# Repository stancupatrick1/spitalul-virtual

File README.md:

<p align="center">
  🌐 <b><a href="https://stancupatrick1.github.io/spitalul-virtual/">stancupatrick1.github.io/spitalul-virtual</a></b> – website, sign-up and live dashboard
</p>

<p align="center">
  <b>Spitalul Virtual</b> (“The Virtual Hospital”) is an open-source health wearable platform.<br>
  It comes in two versions – a <b>smartwatch</b> with a round screen and a slim, <b>screenless band</b> – both built from scratch:<br>
  custom black PCB, silicone case with straps, firmware and a phone web app.
</p>

---

## ✨ Two devices, one platform

<table>
  <tr>
    <th width="50%">⌚ Spitalul Virtual Watch</th>
    <th width="50%">📿 Spitalul Virtual Band</th>
  </tr>
  <tr>
    <td></td>
    <td></td>
  </tr>
  <tr>
    <td>
      <ul>
        <li>1.28" round colour display (GC9A01)</li>
        <li>Heart rate + blood oxygen (MAX30102)</li>
        <li>Step counter (LIS3DH)</li>
        <li>Ø 42 mm round black PCB</li>
        <li>Pod Ø 46.8 × 14 mm, ~250 mAh</li>
      </ul>
    </td>
    <td>
      <ul>
        <li>No screen – LED, vibration and phone app</li>
        <li>Heart rate + SpO2 + <b>skin temperature (TMP117, ±0.1 °C)</b></li>
        <li>Step counter (LIS3DH)</li>
        <li>40 × 24 mm black PCB</li>
        <li>Pod 44 × 28 × 11 mm, ~110 mAh</li>
      </ul>
    </td>
  </tr>
  <tr>
    <td align="center"><a href="watch/"><b>→ watch/</b></a></td>
    <td align="center"><a href="band/"><b>→ band/</b></a></td>
  </tr>
</table>

Both run on an **ESP32-C3** (WiFi + Bluetooth LE), charge over **USB-C** and stream their data to your phone over Bluetooth using the standard Heart Rate, Pulse Oximeter and Health Thermometer services.

## 📱 All-day data in Health Connect (Android) – 🚧 in development

> **🚧 În dezvoltare / In development** – not ready for users yet (not tested on a real band, ROOK upload not connected yet).

The band saves **one record per minute, all day** (the last ~40–45 days). The **[Spitalul Virtual Android app](companion/)** downloads it over Bluetooth and writes it to **Health Connect**. From there the Spitalul Virtual platform imports it through ROOK, like data from any other watch.

```
band ──Bluetooth──▶ Spitalul Virtual app ──▶ Health Connect ──ROOK──▶ Spitalul Virtual platform
```

Test build: **[app-latest](https://github.com/stancupatrick1/spitalul-virtual/releases/tag/app-latest)** (built automatically by GitHub Actions) · step-by-step instructions (RO): [`companion/README.md`](companion/README.md) · protocol: [`band/docs/SYNC_PROTOCOL.md`](band/docs/SYNC_PROTOCOL.md)

## 🔬 The boards

| Watch – skin side | Band – skin side |
|:---:|:---:|
|  |  |

* 2 layers, 1.0 mm, **black solder mask**, white silkscreen, ENIG (gold) pads
* sensors on the skin side, battery side under the cells
* KiCad design-rule check: **0 errors, 0 unconnected pads**
* ready-to-order files for JLCPCB / PCBWay: Gerbers, BOM with LCSC part numbers, pick-and-place

## 🧩 What's inside

```
spitalul-virtual/
├── watch/                    ⌚ smartwatch with a round screen
│   ├── hardware/kicad/       KiCad 7 project (schematic, PCB, footprints, 3D models)
│   ├── hardware/jlcpcb/      Gerbers, BOM, CPL – ready to order
│   ├── mechanical/           silicone case + straps (OpenSCAD, STL), mold, PCB STEP
│   ├── firmware/             ESP32-C3 firmware (PlatformIO / Arduino)
│   └── docs/                 schematic PDF, ordering guide, build guide
└── band/                     📿 slim screenless band
    ├── hardware/  mechanical/  firmware/  docs/   (same layout)
    └── app/                  web app – live data over Web Bluetooth
companion/                    📱 Android app (Flutter): band → Health Connect
```

Every design file is generated from one Python description of the circuit (`*/scripts/design.py`), so the schematic and the PCB always match – run `scripts/make_all.sh` to rebuild a board from scratch.

## 🚀 Build one

1. **Order the PCB** – follow [`watch/docs/ORDERING_JLCPCB.md`](watch/docs/ORDERING_JLCPCB.md) or [`band/docs/ORDERING_JLCPCB.md`](band/docs/ORDERING_JLCPCB.md)
2. **Print or cast the case** – `mechanical/stl/` (TPU 85A–95A or platinum silicone)
3. **Flash the firmware** – `cd firmware && pio run -t upload`
4. **Open the app** – `band/app/index.html` in Chrome, tap *Conectează brățara*

| | |
|:---:|:---:|
|  |  |

## 🗺️ Roadmap

- [x] Schematic + PCB for the watch and the band
- [x] Silicone case, straps and casting molds
- [x] Firmware (heart rate, SpO2, steps, temperature, BLE) and web app
- [ ] First prototype boards
- [ ] Testing on the wrist and calibration
- [x] All-day history on the band + Android app that saves it to Health Connect
- [ ] Test the full path on the Spitalul Virtual platform (ROOK → „Preia din dispozitive”)

## 👋 About us

### Hi, I'm Patrick

I'm **Stancu Patrick**, a middle-school student at **Colegiul Național „Mihai Viteazul” Ploiești**, Romania, who loves building electronics that help people.

| Year | Olimpiada Națională de Creativitate Științifică | Project |
|:---:|:---|:---|
| 🥇 2024 | **Winner** | **SmartBuoy** |
| 🏅 2025 | **Mențiune** (Honourable Mention) | [**ThermoGuard**](https://github.com/stancupatrick1/thermoguard) – ESP32 temperature monitoring for medical fridges and freezers |
| 🔧 2026 | building now | **Spitalul Virtual** – this project |

More of my projects: [ThermoGuard](https://github.com/stancupatrick1/thermoguard) · [PEEPER](https://github.com/stancupatrick1/Project_Peeper) · [my GitHub profile](https://github.com/stancupatrick1)

### Hi, I'm Nicola 👋

I'm a middle-school student at **Colegiul Național „Mihai Viteazul” Ploiești**, Romania. I love learning new things and getting better at them, and right now that means building electronics that help people.

* 🔧 Working on [Spitalul Virtual](https://github.com/stancupatrick1/spitalul-virtual) with my team: improving our open-source health wearables (a smartwatch and a screenless band) and building the phone app that sends their data to a doctor
* 🇷🇴 Based in Ploiești, Romania · I write in English and Romanian

[Nicola's GitHub profile](https://github.com/NicolaGrigore2012)

## ⚠️ Disclaimer

This is a student/hobby project. Heart-rate, SpO2 and temperature readings are estimates and are **not** for medical use or diagnosis.

## 📄 License

[MIT](LICENSE) © 2026 Stancu Patrick – use it, learn from it, build your own.

<p align="center"><sub>made with ❤️ in Romania by Stancu Patrick</sub></p>

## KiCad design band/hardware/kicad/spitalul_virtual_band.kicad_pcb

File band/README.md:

# Spitalul Virtual – Band

**made by Stancu Patrick**

A slim, **screenless** wearable, the little sibling of the Spitalul Virtual smartwatch. It has the same **black PCB** style and the same brains, plus a **skin temperature sensor**:

* ❤️ **heart rate** + 🩸 **blood oxygen (SpO2)** – MAX30102
* 🌡️ **skin temperature** (±0.1 °C) – TMP117
* 👣 **steps** – LIS3DH accelerometer
* 🔋 **USB-C charging**, 📳 vibration motor, 🟢 status LED, side button
* 📱 everything streams to your phone over **Bluetooth LE** (web app included)

| Board – skin side | Board – battery side |
|---|---|
|  |  |

> ⚠️ Hobby project. Heart-rate, SpO2 and temperature values are estimates and are **not** for medical use. The temperature is **skin** temperature (normally 32–35 °C), not body temperature.

---

## Size

| | Watch | **Band** |
|---|---|---|
| Board | Ø 42 mm round | **40 × 24 mm** pill |
| Pod | Ø 46.8 × 14 mm | **44.4 × 28.4 × 11 mm** |
| Screen | 1.28" round | none – LED + vibration + phone app |
| Battery | 402530 (~250 mAh) | 302025 (~110 mAh) |

## What's inside

| Function | Part | LCSC |
|---|---|---|
| Brain, WiFi + Bluetooth LE, USB programming | ESP32-C3-WROOM-02-N4 | C2934560 |
| Heart rate + SpO2 (skin side) | MAX30102EFD+T | C6454833 |
| Skin temperature (skin side, I2C 0x48) | TMP117AIDRVR | C699536 |
| Steps (I2C 0x19) | LIS3DHTR | C15134 |
| Li-Po charger (~210 mA) | MCP73831T-2ACI/OT | C424093 |
| 3.3 V / 1.8 V regulators | ME6211C33M5G-N / XC6206P182MR | C82942 / C347373 |
| USB-C | HRO TYPE-C-31-M-12 | C165948 |
| Side button | EVQ-P7C01P | C388883 |
| Motor driver | AO3400A + 1N4148WS | C20917 / C2128 |
| Status LED (green, top) / charge LED (red, bottom) | 0603 LEDs | C72043 / C2286 |

**Board:** 40 × 24 mm, 2 layers, 1.0 mm, black solder mask, white silkscreen, ENIG. KiCad DRC: see `hardware/kicad/drc_report.txt`.

Hand-soldered to gold pads on the top side: **Li-Po 302025** (3.7 V, with protection circuit) → `B+ B-`, and an **8 mm coin vibration motor** → `M+ M-`.

## Folders

```
hardware/kicad/      KiCad 7 project: schematic, PCB, symbols, footprints, 3D models
hardware/jlcpcb/     ready to upload: gerber zip, BOM, CPL (pick & place)
mechanical/          band (OpenSCAD source + STL), top cap, keeper loop, silicone mold, PCB STEP
firmware/            ESP32-C3 firmware (PlatformIO / Arduino)
app/                 web app (Web Bluetooth) - live HR / SpO2 / temperature / steps
docs/                schematic PDF, layer PDFs, pictures, ordering + build guide
scripts/             Python that generates the whole design (re-run make_all.sh)
```

## Order at JLCPCB

See **[docs/ORDERING_JLCPCB.md](docs/ORDERING_JLCPCB.md)**: upload `hardware/jlcpcb/spitalul_virtual_band_gerbers.zip`, choose **1.0 mm, black, ENIG**, then `spitalul_virtual_band_BOM.csv` + `spitalul_virtual_band_CPL.csv` for assembly. Parts are on **both sides** (sensors face the skin).

## Band

`mechanical/stl/band_silicone_with_straps.stl` is one piece (pod + straps). Print in **TPU 85A–95A** or cast **silicone** with the mold in `mechanical/stl/mold/`. `band_top_cap.stl` is the rigid top window – print it in **clear PETG or clear resin** so the green LED shines through. Details in **[docs/BUILD_GUIDE.md](docs/BUILD_GUIDE.md)**.

## Firmware + app

```
cd firmware && pio run -t upload      # hold the side button while plugging USB-C in the first time
```

* **Button:** tap = battery level on the LED (1–3 blinks), double tap = vibrate, hold 3 s = off (tap to wake).
* **Bluetooth:** advertises as **"Spitalul Virtual Band"** with the standard Heart Rate, Health Thermometer, Pulse Oximeter and Battery services, plus a Spitalul Virtual service.
* **App:** open `app/index.html` in Chrome (Android / Windows / Mac / Linux), or put the repo on GitHub Pages and open `https://<you>.github.io/<repo>/app/`. Tap **Conectează brățara**.

## Regenerate everything

```
cd scripts && ./make_all.sh     # KiCad 7, Python 3 (shapely, numpy, cairosvg, cadquery), OpenSCAD
```

## License

MIT – see [LICENSE](LICENSE). © 2026 Stancu Patrick.

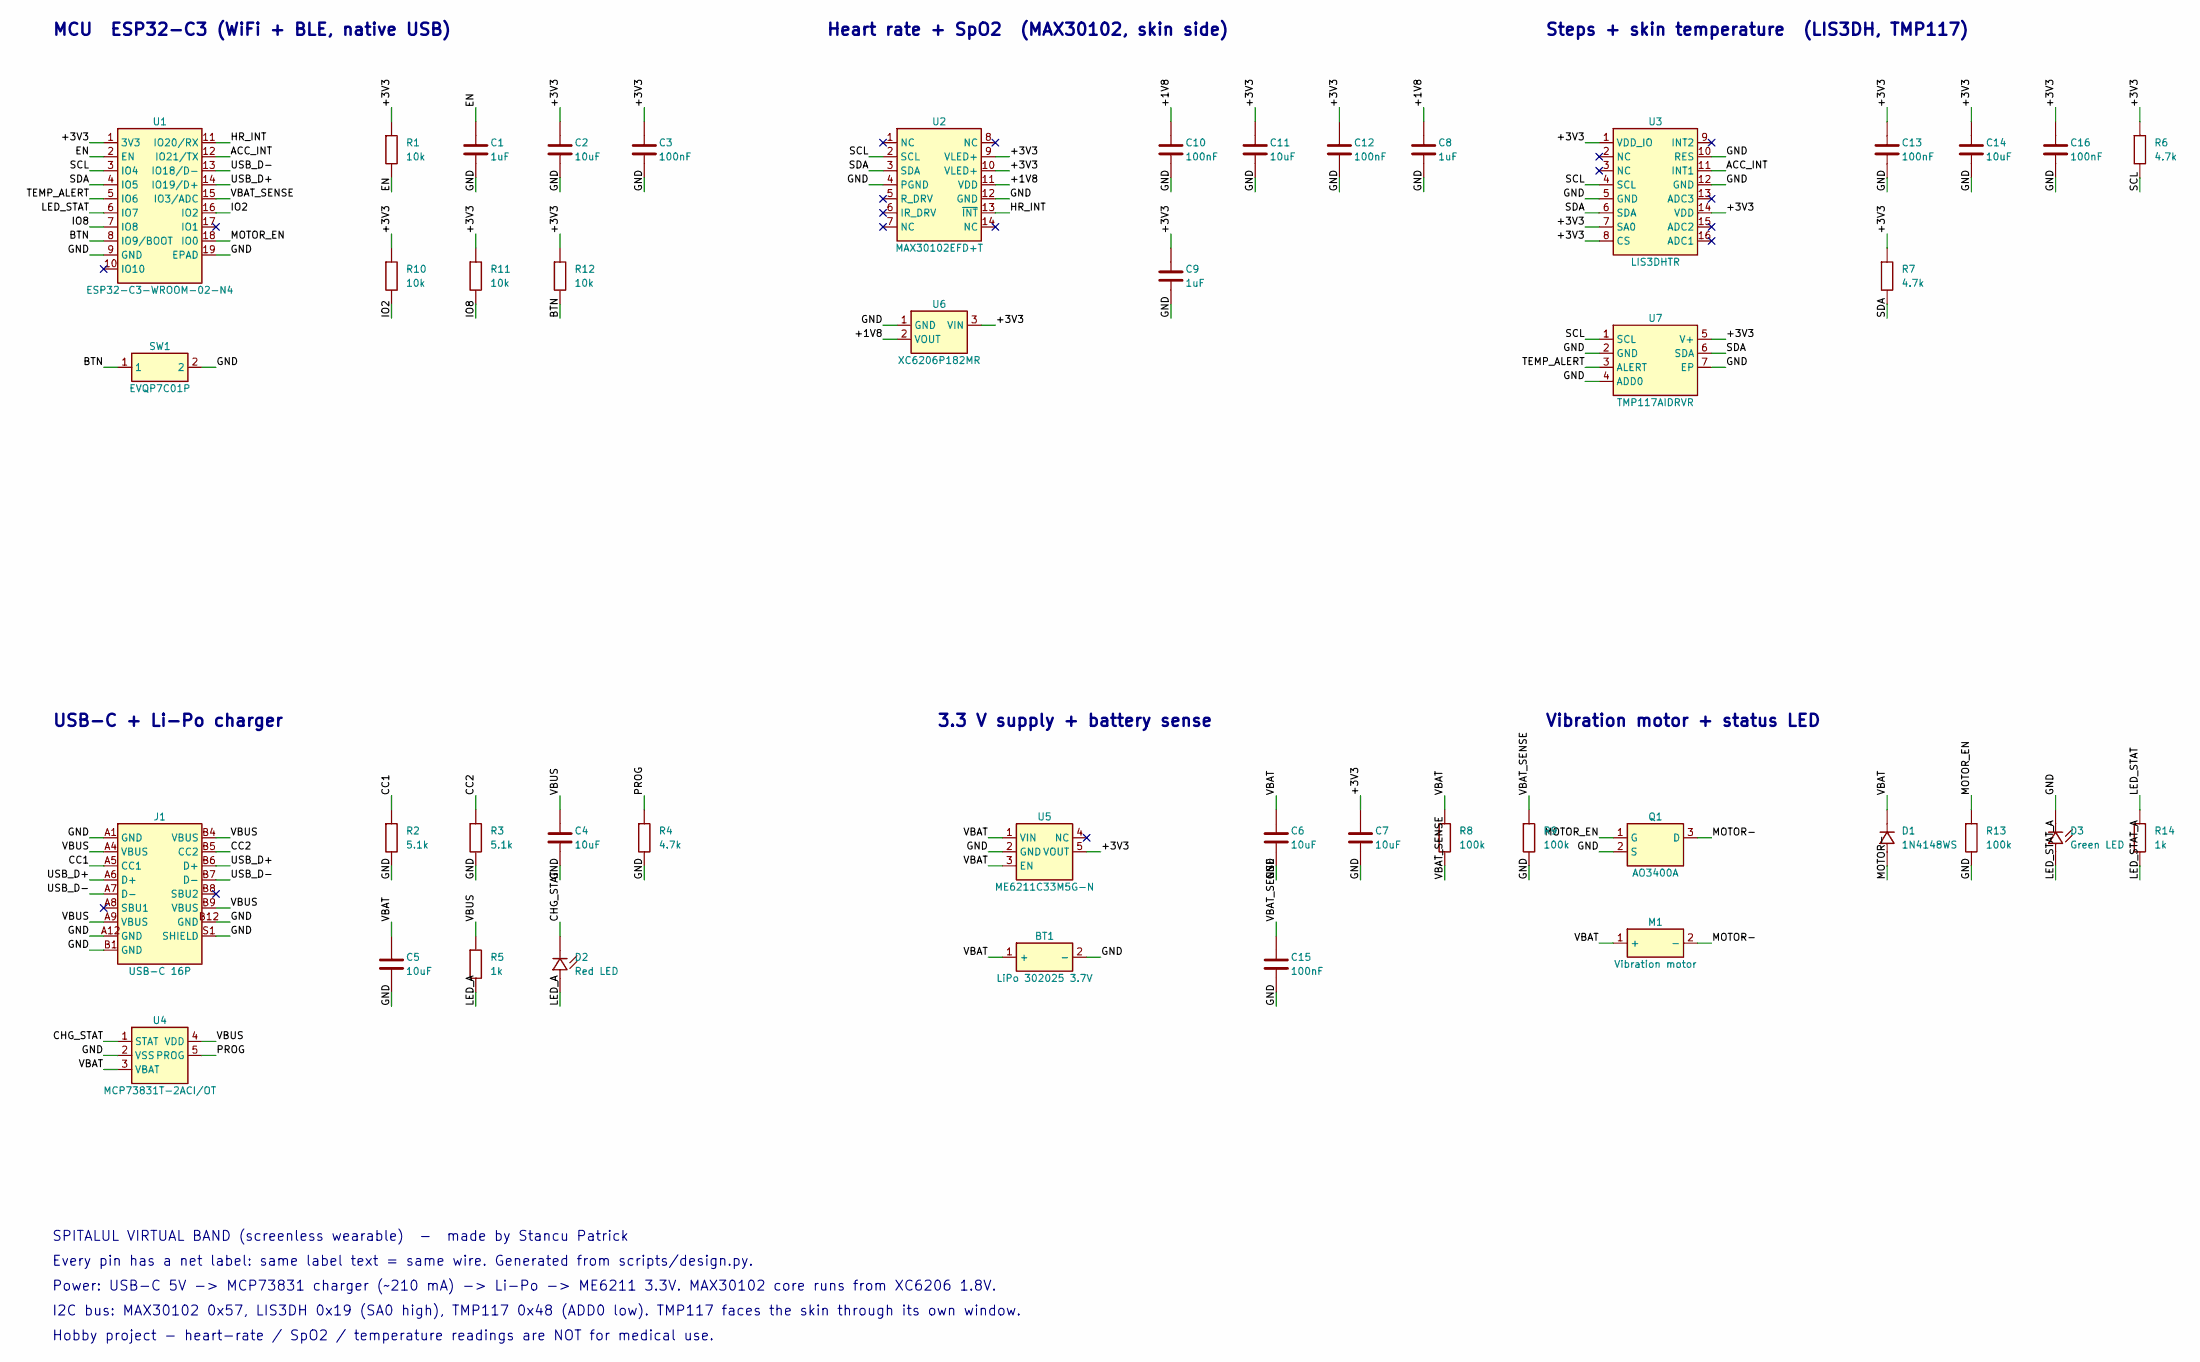
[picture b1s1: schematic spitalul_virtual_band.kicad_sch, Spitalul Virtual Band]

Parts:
BT1: LiPo 302025 3.7V; BatteryPads
C1, C8, C9: 1uF; C_0402_1005Metric; LCSC C52923
C2, C4, C5, C6, C7, C11, C14: 10uF; C_0603_1608Metric; LCSC C19702
C3, C10, C12, C13, C15, C16: 100nF; C_0402_1005Metric; LCSC C1525
D1: 1N4148WS; D_SOD-323; LCSC C2128
D2: Red LED; LED_0603_1608Metric; LCSC C2286
D3: Green LED; LED_0603_1608Metric; LCSC C72043
J1: USB-C 16P; USB_C_Receptacle_HRO_TYPE-C-31-M-12; LCSC C165948
M1: Vibration motor; MotorPads
Q1: AO3400A; SOT-23; LCSC C20917
R1, R10, R11, R12: 10k; R_0402_1005Metric; LCSC C25744
R2, R3: 5.1k; R_0402_1005Metric; LCSC C25905
R4, R6, R7: 4.7k; R_0402_1005Metric; LCSC C25900
R5, R14: 1k; R_0402_1005Metric; LCSC C11702
R8, R9, R13: 100k; R_0402_1005Metric; LCSC C25741
SW1: EVQP7C01P; SW_SPST_EVQP7C; LCSC C388883
U1: ESP32-C3-WROOM-02-N4; ESP32-C3-WROOM-02; LCSC C2934560
U2: MAX30102EFD+T; Maxim_OLGA-14_3.3x5.6mm_P0.8mm; LCSC C6454833
U3: LIS3DHTR; LGA-16_3x3mm_P0.5mm_LayoutBorder3x5y; LCSC C15134
U4: MCP73831T-2ACI/OT; SOT-23-5; LCSC C424093
U5: ME6211C33M5G-N; SOT-23-5; LCSC C82942
U6: XC6206P182MR; SOT-23; LCSC C347373
U7: TMP117AIDRVR; WSON-6-1EP_2x2mm_P0.65mm_EP1x1.6mm; LCSC C699536

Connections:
+1V8: C8.1, C10.1, U2.11 (VDD), U6.2 (VOUT)
+3V3: C2.1, C3.1, C7.1, C9.1, C11.1, C12.1, C13.1, C14.1, C16.1, R1.1, R6.1, R7.1, R10.1, R11.1, R12.1, U1.1 (3V3), U2.9 (VLED+), U2.10 (VLED+), U3.1 (VDD_IO), U3.7 (SA0), U3.8 (CS), U3.14 (VDD), U5.5 (VOUT), U6.3 (VIN), U7.5 (V+)
ACC_INT: U1.12 (IO21/TX), U3.11 (INT1)
BTN: R12.2, SW1.1, U1.8 (IO9/BOOT)
CC1: J1.A5 (CC1), R2.1
CC2: J1.B5 (CC2), R3.1
CHG_STAT: D2.1, U4.1 (STAT)
EN: C1.1, R1.2, U1.2 (EN)
GND: BT1.2 (-), C1.2, C2.2, C3.2, C4.2, C5.2, C6.2, C7.2, C8.2, C9.2, C10.2, C11.2, C12.2, C13.2, C14.2, C15.2, C16.2, D3.1, J1.A1 (GND), J1.A12 (GND), J1.B1 (GND), J1.B12 (GND), J1.S1 (SHIELD), Q1.2 (S), R2.2, R3.2, R4.2, R9.2, R13.2, SW1.2, U1.9 (GND), U1.19 (EPAD), U2.4 (PGND), U2.12 (GND), U3.5 (GND), U3.10 (RES), U3.12 (GND), U4.2 (VSS), U5.2 (GND), U6.1 (GND), U7.2 (GND), U7.4 (ADD0), U7.7 (EP)
HR_INT: U1.11 (IO20/RX), U2.13 (~INT)
IO2: R10.2, U1.16 (IO2)
IO8: R11.2, U1.7 (IO8)
LED_A: D2.2, R5.2
LED_STAT: R14.1, U1.6 (IO7)
LED_STAT_A: D3.2, R14.2
MOTOR-: D1.2, M1.2 (-), Q1.3 (D)
MOTOR_EN: Q1.1 (G), R13.1, U1.18 (IO0)
PROG: R4.1, U4.5 (PROG)
SCL: R6.2, U1.3 (IO4), U2.2 (SCL), U3.4 (SCL), U7.1 (SCL)
SDA: R7.2, U1.4 (IO5), U2.3 (SDA), U3.6 (SDA), U7.6 (SDA)
TEMP_ALERT: U1.5 (IO6), U7.3 (ALERT)
USB_D+: J1.A6 (D+), J1.B6 (D+), U1.14 (IO19/D+)
USB_D-: J1.A7 (D-), J1.B7 (D-), U1.13 (IO18/D-)
VBAT: BT1.1 (+), C5.1, C6.1, D1.1, M1.1 (+), R8.1, U4.3 (VBAT), U5.1 (VIN), U5.3 (EN)
VBAT_SENSE: C15.1, R8.2, R9.1, U1.15 (IO3/ADC)
VBUS: C4.1, J1.A4 (VBUS), J1.A9 (VBUS), J1.B4 (VBUS), J1.B9 (VBUS), R5.1, U4.4 (VDD)

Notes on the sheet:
MCU ESP32-C3 (WiFi + BLE, native USB)
Heart rate + SpO2 (MAX30102, skin side)
Steps + skin temperature (LIS3DH, TMP117)
USB-C + Li-Po charger
3.3 V supply + battery sense
Vibration motor + status LED
SPITALUL VIRTUAL BAND (screenless wearable) - made by Stancu Patrick
Every pin has a net label: same label text = same wire. Generated from scripts/design.py.
Power: USB-C 5V -> MCP73831 charger (~210 mA) -> Li-Po -> ME6211 3.3V. MAX30102 core runs from XC6206 1.8V.
I2C bus: MAX30102 0x57, LIS3DH 0x19 (SA0 high), TMP117 0x48 (ADD0 low). TMP117 faces the skin through its own window.
Hobby project - heart-rate / SpO2 / temperature readings are NOT for medical use.

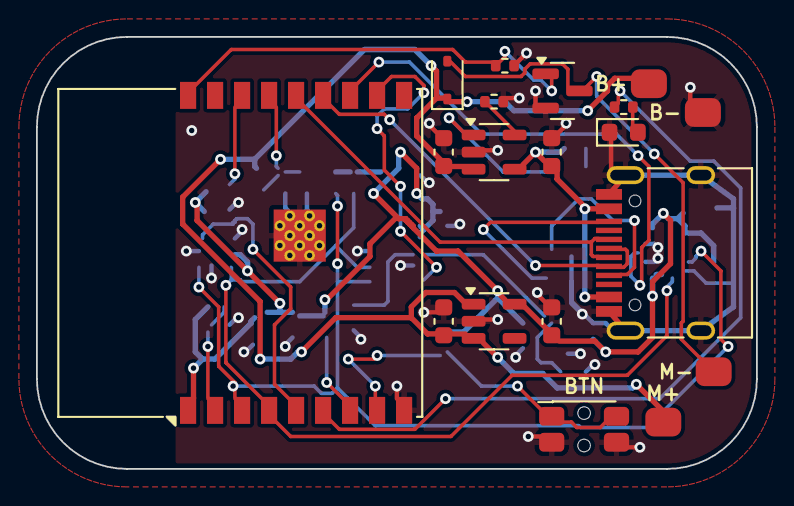
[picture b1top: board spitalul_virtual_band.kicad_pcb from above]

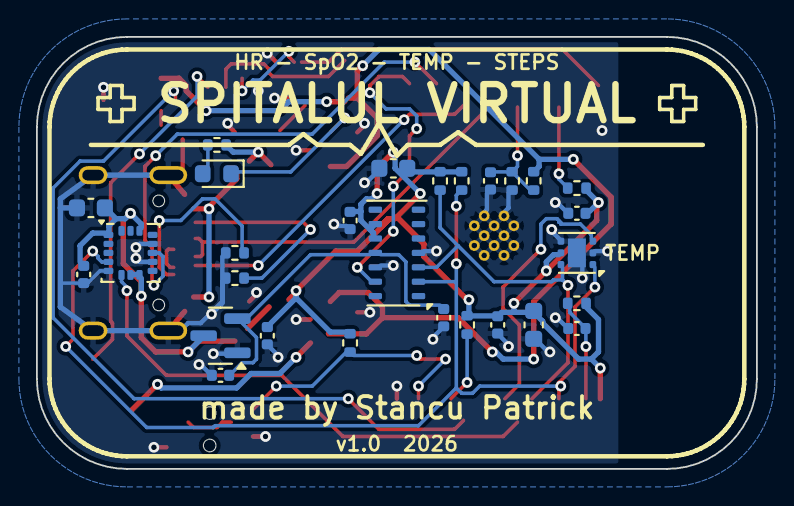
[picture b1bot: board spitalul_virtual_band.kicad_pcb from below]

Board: 2 copper layers, 40.0 x 24.0 mm, 45 parts (28 on the bottom side), 26 nets.

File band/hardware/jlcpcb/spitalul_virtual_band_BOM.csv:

Comment,Designator,Footprint,LCSC Part #
1uF,"C1,C8,C9",C_0402_1005Metric,C52923
100nF,"C3,C10,C12,C13,C15,C16",C_0402_1005Metric,C1525
10uF,"C2,C4,C5,C6,C7,C11,C14",C_0603_1608Metric,C19702
1N4148WS,D1,D_SOD-323,C2128
Red LED,D2,LED_0603_1608Metric,C2286
Green LED,D3,LED_0603_1608Metric,C72043
USB-C 16P,J1,USB_C_Receptacle_HRO_TYPE-C-31-M-12,C165948
AO3400A,Q1,SOT-23,C20917
10k,"R1,R10,R11,R12",R_0402_1005Metric,C25744
100k,"R8,R9,R13",R_0402_1005Metric,C25741
1k,"R5,R14",R_0402_1005Metric,C11702
5.1k,"R2,R3",R_0402_1005Metric,C25905
4.7k,"R4,R6,R7",R_0402_1005Metric,C25900
EVQP7C01P,SW1,SW_SPST_EVQP7C,C388883
ESP32-C3-WROOM-02-N4,U1,ESP32-C3-WROOM-02,C2934560
MAX30102EFD+T,U2,Maxim_OLGA-14_3.3x5.6mm_P0.8mm,C6454833
LIS3DHTR,U3,LGA-16_3x3mm_P0.5mm_LayoutBorder3x5y,C15134
MCP73831T-2ACI/OT,U4,SOT-23-5,C424093
ME6211C33M5G-N,U5,SOT-23-5,C82942
XC6206P182MR,U6,SOT-23,C347373
TMP117AIDRVR,U7,WSON-6-1EP_2x2mm_P0.65mm_EP1x1.6mm,C699536

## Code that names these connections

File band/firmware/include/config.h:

#pragma once
// ===================== Spitalul Virtual BAND - pin map (matches the KiCad board) =====================
#define PIN_SDA         5   // MAX30102 + LIS3DH + TMP117
#define PIN_SCL         4
#define PIN_HR_INT     20   // MAX30102 INT (active low, polled in firmware)
#define PIN_ACC_INT    21   // LIS3DH INT1
#define PIN_TEMP_ALERT  6   // TMP117 ALERT (open drain)
#define PIN_LED         7   // green status LED (active high)
#define PIN_BUTTON      9   // side button, active low (also BOOT)
#define PIN_MOTOR       0   // vibration motor MOSFET gate
#define PIN_VBAT        3   // battery / 2 (100k / 100k divider)

#define ADDR_TMP117   0x48
#define ADDR_LIS3DH   0x19  // SA0 tied to 3.3 V

#define DEVICE_NAME   "Spitalul Virtual Band"
